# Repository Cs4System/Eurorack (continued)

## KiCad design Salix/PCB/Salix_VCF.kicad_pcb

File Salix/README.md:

# Blattwerk Salix VCF

- VCF based on the Moog Transistor Ladder Filter
- Compensation for loss of bass in high resonance settings via potentiometer
- 6,12,18,24 dB/Oct selectable via potentiometer or CV!
- 2 Inputs with attenuator for audio and CV
- Seperate V/Oct input.
- Input-Drive indicator LED
- 8HP
- small and dense SMD build (0603, SOIC, SOT-363!) Not a beginner build, please be sure to have some SMD-soldering practice!
- 45mA @ +12V and 25mA @ -12V
- quick demo:  https://youtu.be/XMdGtwIK5IQ

- All files are published under CC BY-NC-SA 4.0 
- DO NOT USE COMMERCIALLY!
- Build for yourself or for a friend, but do not sell builds, PCBs, pannels or any parts of the designes in this repository! 
- Feel free to modify, copy and use all files provided here. If you want to publish derivative work, please do so under same license as original

- Any feedback and collaboration is very welcome!
- Please feel free to [open an issue on the issues tab](https://github.com/Cs4System/Eurorack/issues)

## How to get involved:
For ongoing discussion see:
https://www.modwiggler.com/forum/viewtopic.php?f=17&t=244412&p=3457366#p3457366

## Order

- The [original version](https://github.com/Cs4System/Eurorack/tree/main/Transistor_Ladder_VCF) PCB and Panel are be available at [sythCube](https://synthcube.com/cart/lorenz-neumann-diy-transistor-ladder-filter)
- Direct order: If you are interested in a set of PCB+Panel, please write a mail to: blattwerk-audio [at] posteo.de or let me know via [Modwiggler](https://www.modwiggler.com/forum/viewtopic.php?f=17&t=244412&p=3457366#p3457366)

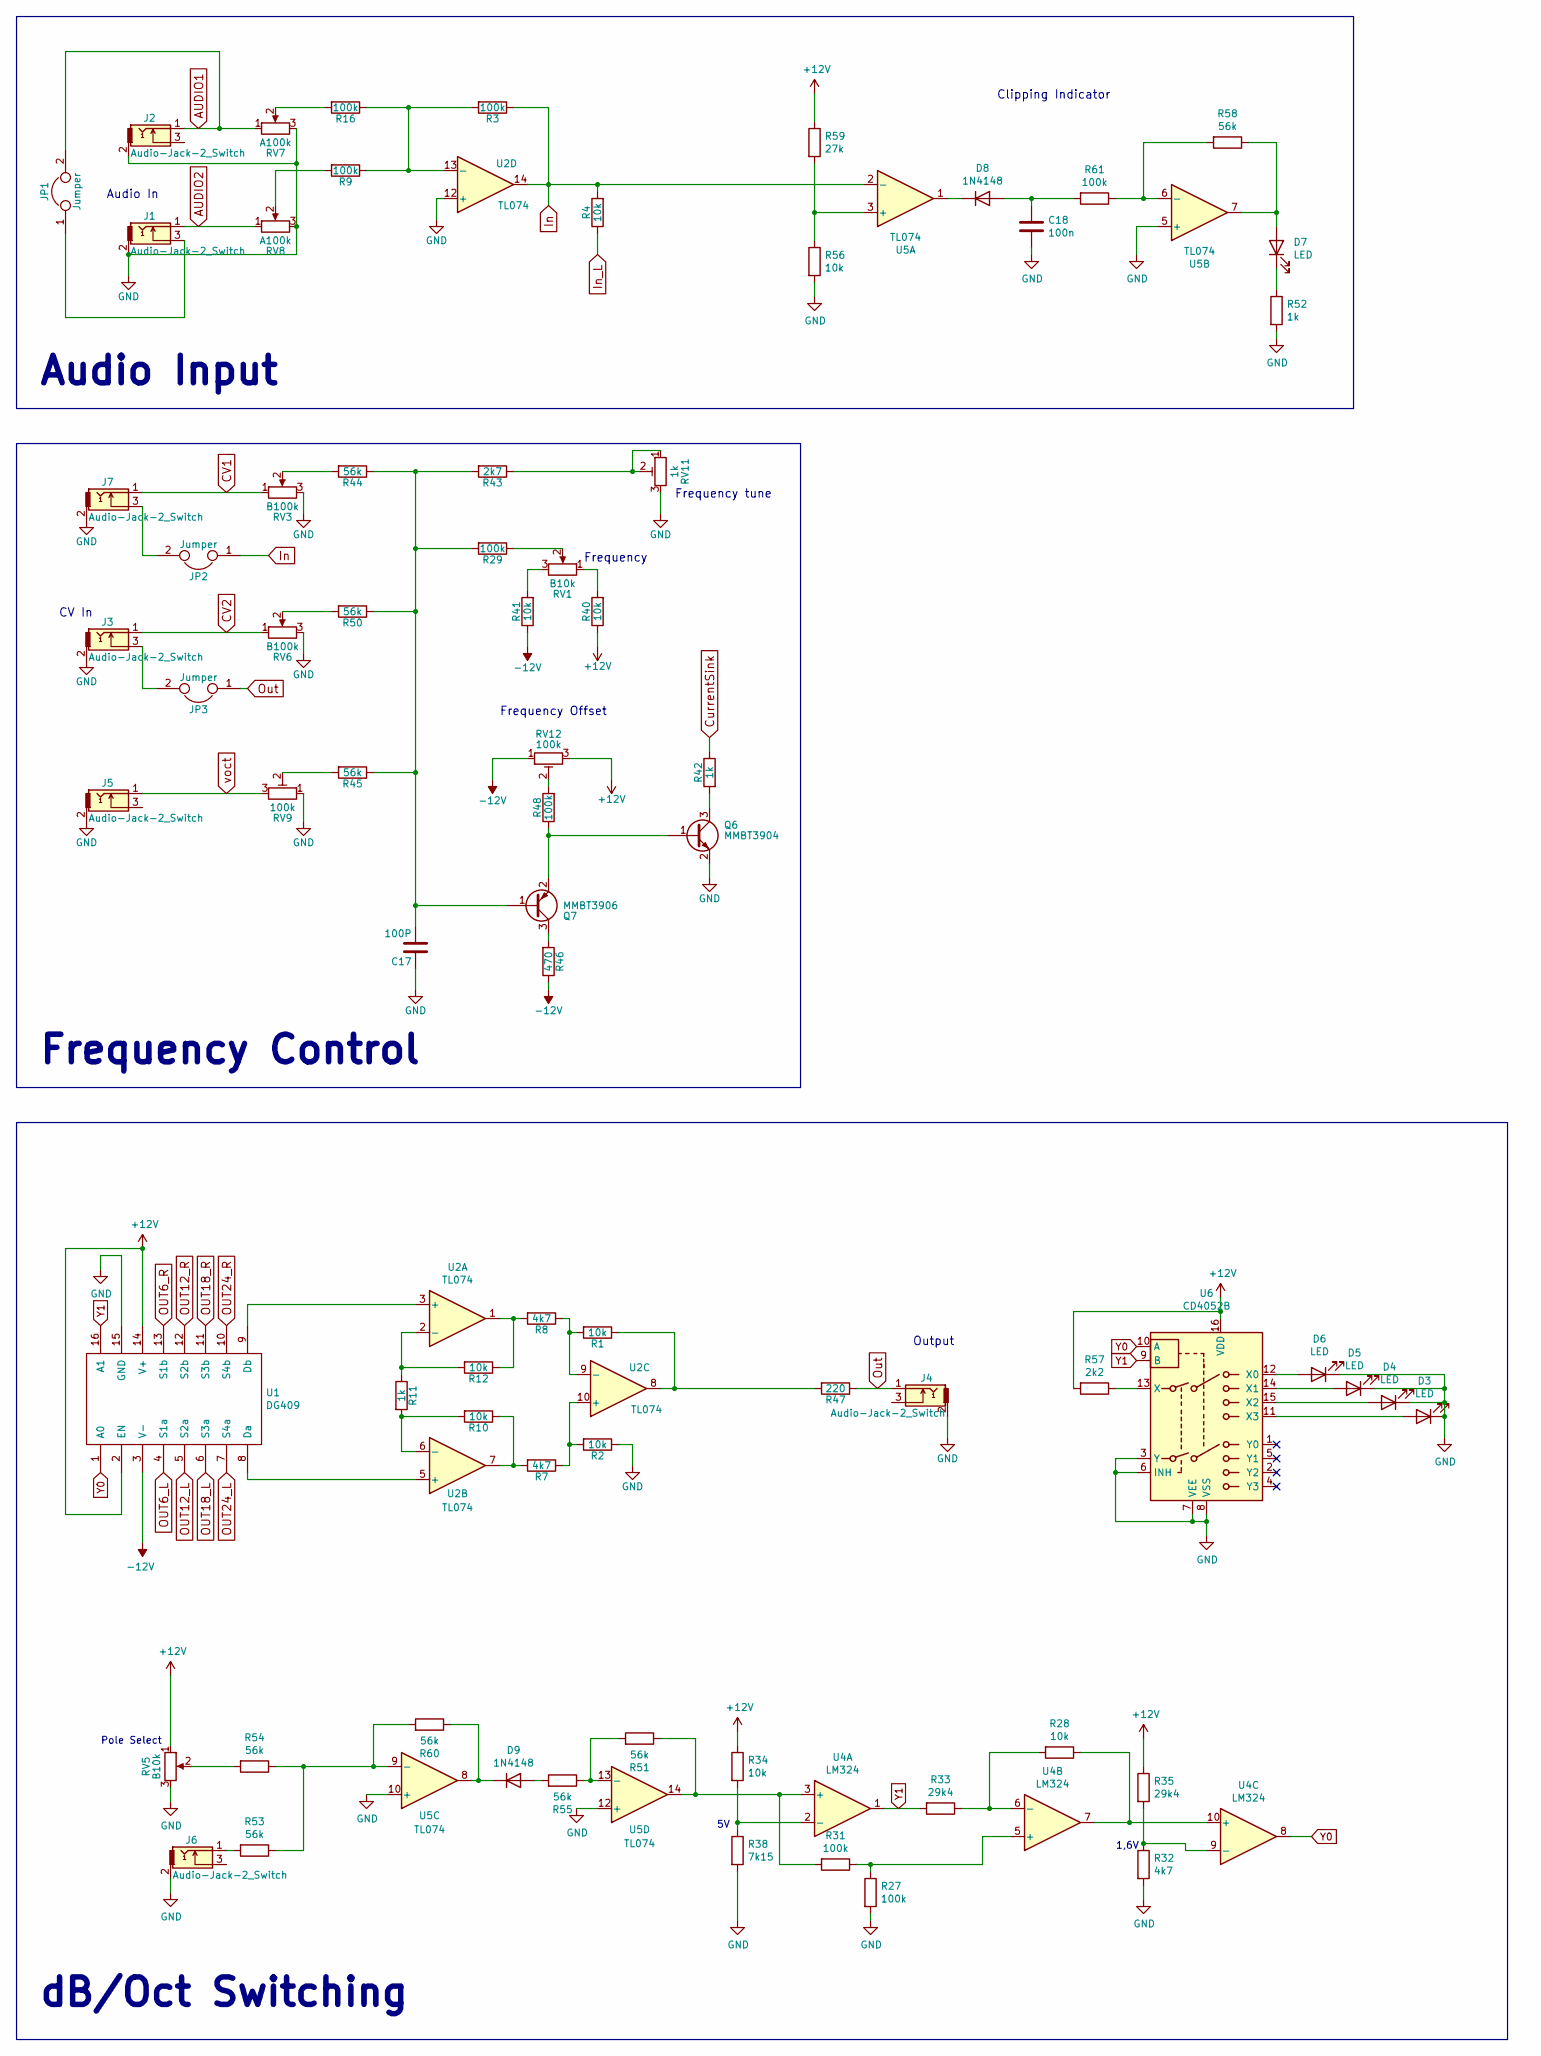
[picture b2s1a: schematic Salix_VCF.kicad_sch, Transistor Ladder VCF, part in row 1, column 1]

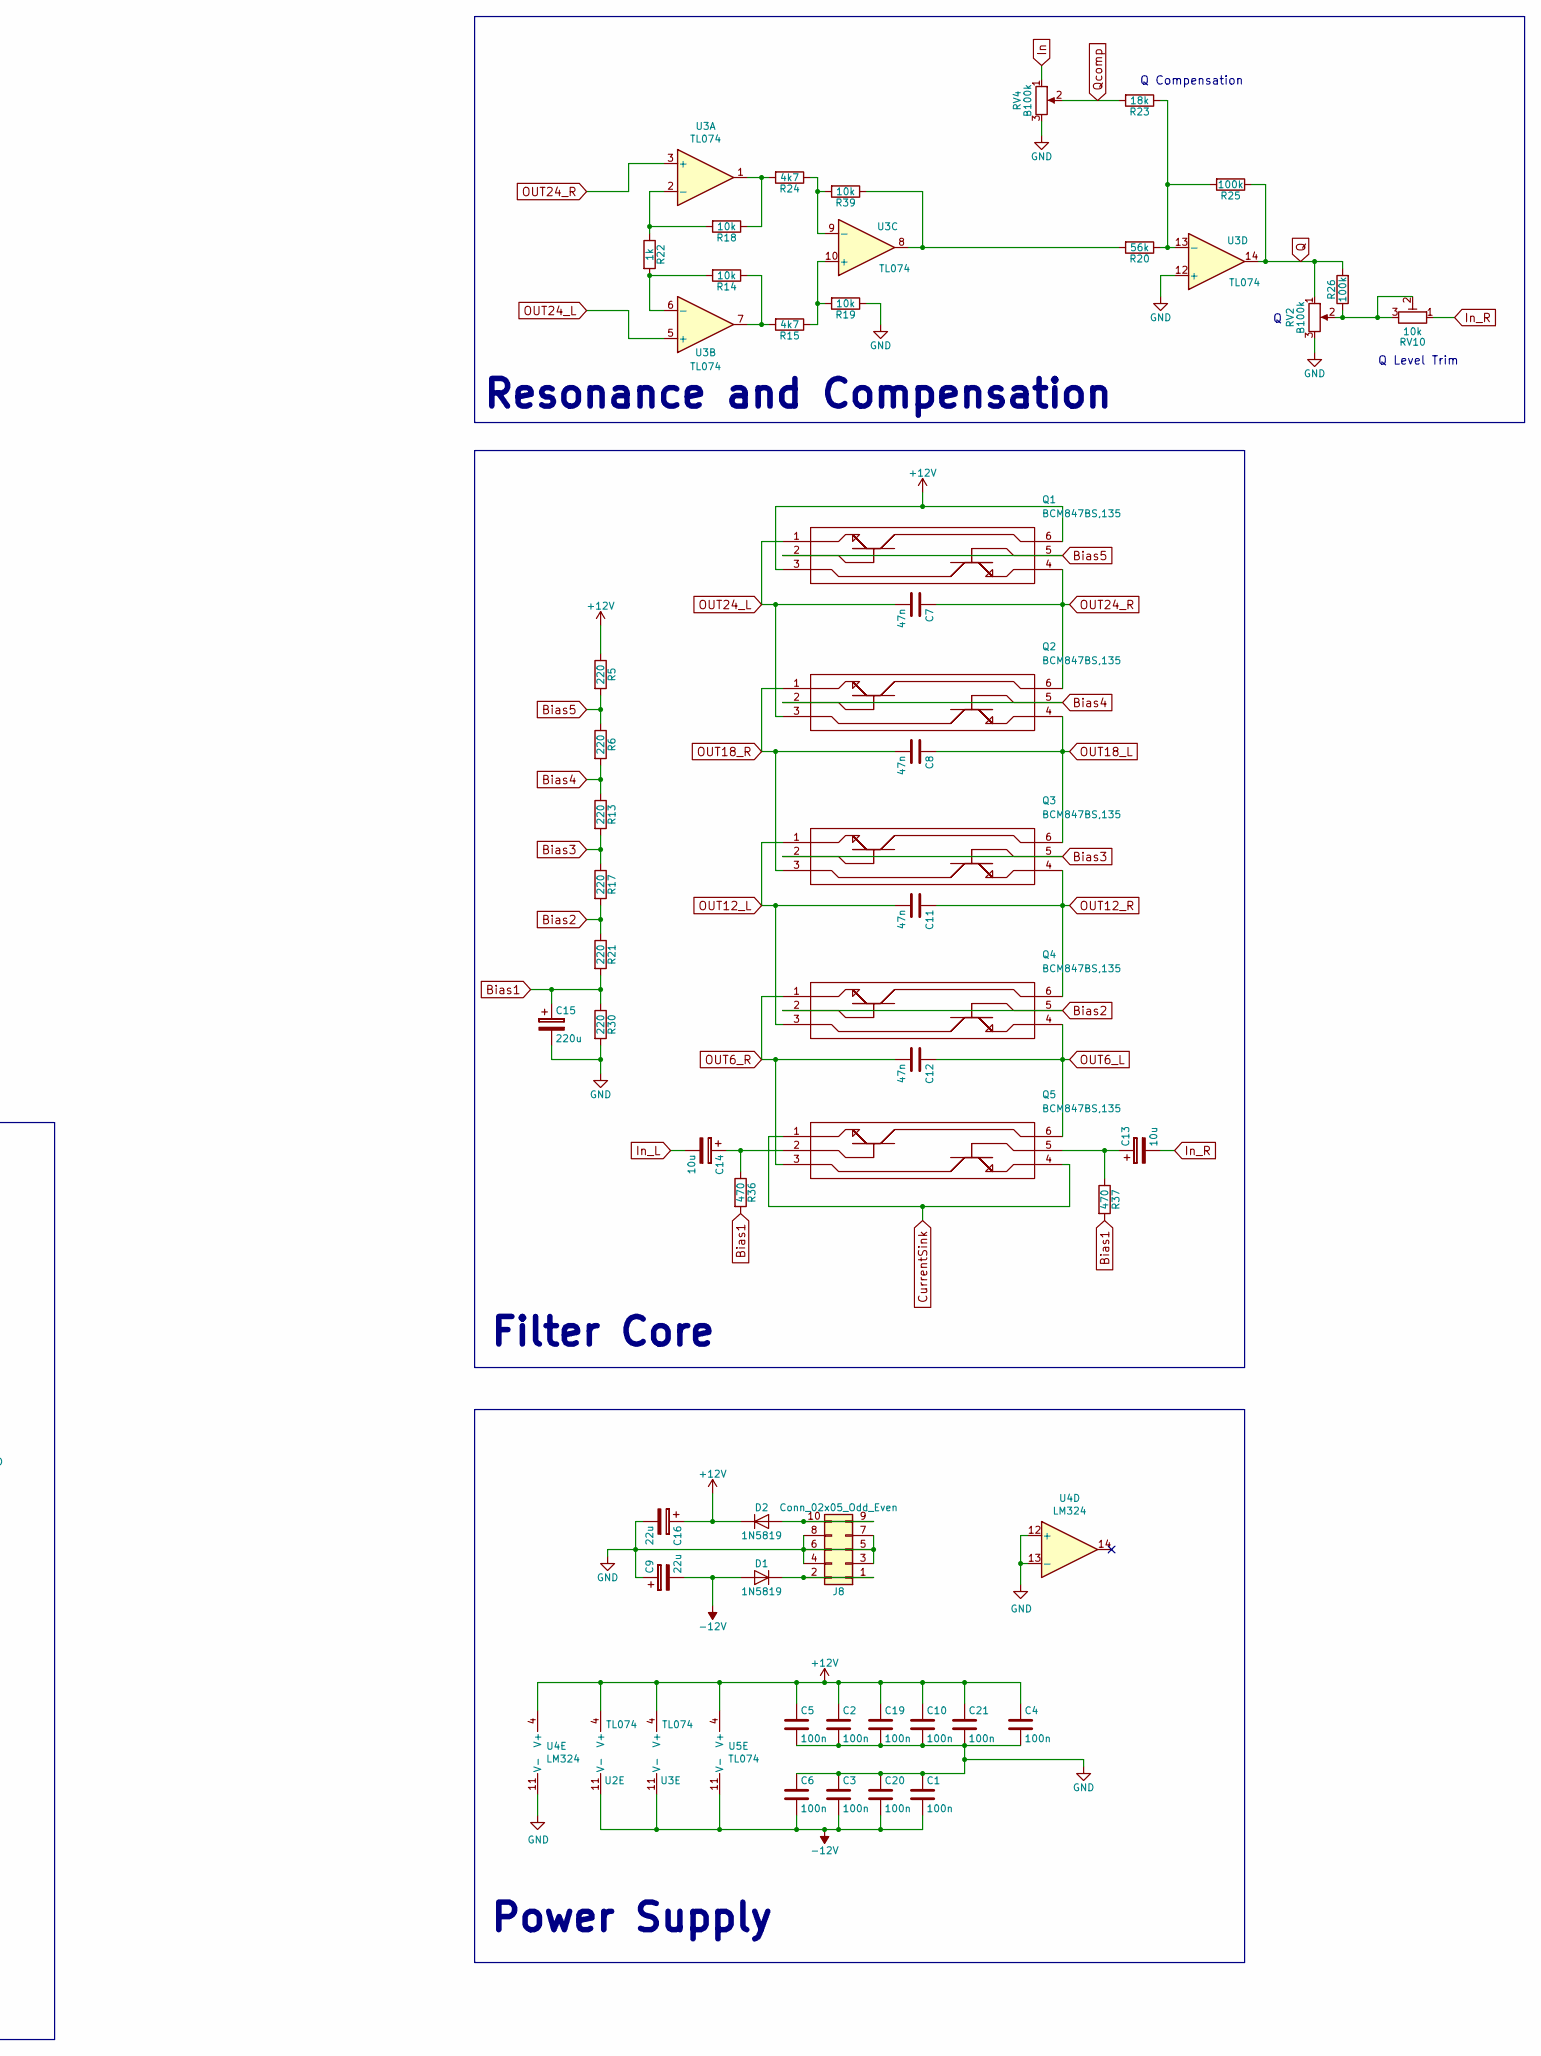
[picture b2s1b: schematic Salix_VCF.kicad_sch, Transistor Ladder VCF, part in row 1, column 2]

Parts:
C1, C2, C3, C4, C5, C6, C10, C18, C19, C20, C21: 100n; C_0603_1608Metric_Pad1.08x0.95mm_HandSolder
C7, C8, C11, C12: 47n; C_Rect_L7.2mm_W2.5mm_P5.00mm_FKS2_FKP2_MKS2_MKP2
C9, C16: 22u; CP_Elec_4x5.7
C13, C14: 10u; CP_Elec_4x5.7
C15: 220u; CP_Elec_6.3x7.7
C17: 100P; C_0603_1608Metric_Pad1.08x0.95mm_HandSolder
D1, D2: 1N5819; D_SOD-123
D3, D4, D5, D6, D7: LED; LED_D3.0mm
D8, D9: 1N4148; D_SOD-323_HandSoldering
J1, J5, J6: Audio-Jack-2_Switch; Thonkicon
J2, J3: Audio-Jack-2_Switch; Thonkicon_noGND
J4: Audio-Jack-2_Switch; Thonkicon_odd
J7: Audio-Jack-2_Switch; Thonkicon_odd2
J8: Conn_02x05_Odd_Even; Multicomp_MC9A12-1034_2x05x2.54mm_Straight
JP1, JP2, JP3: Jumper; PinHeader_1x02_P2.54mm_Vertical
Q1, Q2, Q3, Q4, Q5: BCM847BS,135; SOT-363_SC-70-6_Handsoldering; Manufacturer_Part_Number BCM847BS,135; Mouser Part Number 771-BCM847BS135
Q6: MMBT3904; SOT-23
Q7: MMBT3906; SOT-23
R1, R2, R4, R10, R12, R14, R18, R19, R28, R34, R39, R40, R41, R56: 10k; R_0603_1608Metric_Pad0.98x0.95mm_HandSolder
R3, R9, R16, R25, R26, R27, R29, R31, R48, R61: 100k; R_0603_1608Metric_Pad0.98x0.95mm_HandSolder
R5, R6, R13, R17, R21, R30, R47: 220; R_0603_1608Metric_Pad0.98x0.95mm_HandSolder
R7, R8, R15, R24, R32: 4k7; R_0603_1608Metric_Pad0.98x0.95mm_HandSolder
R11, R22, R42, R52: 1k; R_0603_1608Metric_Pad0.98x0.95mm_HandSolder
R20, R44, R45, R50, R51, R53, R54, R55, R58, R60: 56k; R_0603_1608Metric_Pad0.98x0.95mm_HandSolder
R23: 18k; R_0603_1608Metric_Pad0.98x0.95mm_HandSolder
R33, R35: 29k4; R_0603_1608Metric_Pad0.98x0.95mm_HandSolder
R36, R37, R46: 470; R_0603_1608Metric_Pad0.98x0.95mm_HandSolder
R38: 7k15; R_0603_1608Metric_Pad0.98x0.95mm_HandSolder
R43: 2k7; R_0603_1608Metric_Pad0.98x0.95mm_HandSolder
R57: 2k2; R_0603_1608Metric_Pad0.98x0.95mm_HandSolder
R59: 27k; R_0603_1608Metric_Pad0.98x0.95mm_HandSolder
RV1, RV5: B10k; Potentiometer_Alps_RK09K_Horizontal
RV2, RV3, RV4, RV6: B100k; Potentiometer_Alps_RK09K_Horizontal
RV7, RV8: A100k; Potentiometer_Alps_RK09K_Horizontal
RV9, RV12: 100k; Trim_pot
RV10: 10k; Trim_pot
RV11: 1k; Trim_pot
U1: DG409; SOIC-16_3.9x9.9mm_P1.27mm
U2, U3, U5: TL074; SOIC-14_3.9x8.7mm_P1.27mm
U4: LM324; SOIC-14_3.9x8.7mm_P1.27mm
U6: CD4052B; SOIC-16W_5.3x10.2mm_P1.27mm

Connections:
+12V: C2.1, C4.1, C5.1, C10.1, C16.1, C19.1, C21.1, D2.1 (K), Q1.3, Q1.6, R5.1, R34.1, R35.1, R40.1, R57.2, R59.1, RV5.1, RV12.3, U1.2 (EN), U1.14 (V+), U2.4 (V+), U3.4 (V+), U4.4 (V+), U5.4 (V+), U6.16 (VDD)
-12V: C1.2, C3.2, C6.2, C9.2, C20.2, D1.2 (A), R41.1, R46.1, RV12.1, U1.3 (V-), U2.11 (V-), U3.11 (V-), U5.11 (V-)
AUDIO1: J2.1, JP1.2, RV7.1
AUDIO2: J1.1, RV8.1
Bias1: C15.1, R21.2, R30.1, R36.2, R37.2
Bias2: Q4.2, Q4.5, R17.2, R21.1
Bias3: Q3.2, Q3.5, R13.2, R17.1
Bias4: Q2.2, Q2.5, R6.2, R13.1
Bias5: Q1.2, Q1.5, R5.2, R6.1
CV1: J7.1, RV3.1
CV2: J3.1, RV6.1
CurrentSink: Q5.1, Q5.4, R42.1
GND: C1.1, C2.2, C3.1, C4.2, C5.2, C6.1, C9.1, C10.2, C15.2, C16.2, C17.1, C18.2, C19.2, C20.1, C21.2, D3.1 (K), D4.1 (K), D5.1 (K), D6.1 (K), J1.2, J2.2, J3.2, J4.2, J5.2, J6.2, J7.2, J8.3, J8.4, J8.5, J8.6, J8.7, J8.8, Q6.2 (E), R2.1, R19.1, R27.2, R30.2, R32.2, R38.2, R52.2, R56.2, RV2.3, RV3.3, RV4.3, RV5.3, RV6.3, RV7.3, RV8.3, RV9.1, RV11.3, U1.15 (GND), U2.12 (+), U3.12 (+), U4.11 (V-), U4.12 (+), U4.13 (-), U5.5 (+), U5.10 (+), U5.12 (+), U6.3 (Y), U6.6 (INH), U6.7 (VEE), U6.8 (VSS)
In: JP2.1, R3.1, R4.2, RV4.1, U2.14, U5.2 (-)
In_L: C14.2, R4.1
In_R: C13.2, RV10.1
unnamed: C13.1, Q5.5, R37.1
unnamed: C14.1, Q5.2, R36.1
unnamed: D1.1 (K), J8.1, J8.2
unnamed: D2.2 (A), J8.9, J8.10
unnamed: D3.2 (A), U6.11 (X3)
unnamed: D4.2 (A), U6.15 (X2)
unnamed: D5.2 (A), U6.14 (X1)
unnamed: D6.2 (A), U6.12 (X0)
unnamed: D7.2 (A), R58.1, U5.7
unnamed: D7.1 (K), R52.1
unnamed: C18.1, D8.2 (A), R61.2
unnamed: D8.1 (K), U5.1
unnamed: D9.2 (A), R55.2
unnamed: D9.1 (K), R60.1, U5.8
unnamed: J1.3, JP1.1
unnamed: J3.3, JP3.2
unnamed: J6.1, R53.2
unnamed: J7.3, JP2.2
unnamed: Q6.1 (B), Q7.2 (E), R48.1
unnamed: Q6.3 (C), R42.2
unnamed: C17.2, Q7.1 (B), R29.2, R43.2, R44.1, R45.1, R50.1
unnamed: Q7.3 (C), R46.2
unnamed: R1.1, R47.2, U2.8
unnamed: R9.2, RV8.2
unnamed: R7.2, R10.1, U2.7
unnamed: R8.2, R12.1, U2.1
unnamed: R14.1, R15.2, U3.7
unnamed: R16.2, RV7.2
unnamed: R18.1, R24.2, U3.1
unnamed: R20.2, R39.1, U3.8
unnamed: R26.1, RV2.2, RV10.2, RV10.3
unnamed: R29.1, RV1.2
unnamed: R40.2, RV1.1
unnamed: R41.2, RV1.3
unnamed: R43.1, RV11.1, RV11.2
unnamed: R44.2, RV3.2
unnamed: R45.2, RV9.2
unnamed: R48.2, RV12.2
unnamed: R50.2, RV6.2
unnamed: R54.2, RV5.2
unnamed: U1.8 (Da), U2.5 (+)
unnamed: U1.9 (Db), U2.3 (+)
unnamed: R11.1, R12.2, U2.2 (-)
unnamed: R10.2, R11.2, U2.6 (-)
unnamed: R2.2, R7.1, U2.10 (+)
unnamed: R1.2, R8.1, U2.9 (-)
unnamed: R3.2, R9.1, R16.1, U2.13 (-)
unnamed: R18.2, R22.1, U3.2 (-)
unnamed: R14.2, R22.2, U3.6 (-)
unnamed: R15.1, R19.2, U3.10 (+)
unnamed: R24.1, R39.2, U3.9 (-)
unnamed: R20.1, R23.1, R25.2, U3.13 (-)
unnamed: R31.2, R51.1, U4.3 (+), U5.14
unnamed: R34.2, R38.1, U4.2 (-)
unnamed: R27.1, R31.1, U4.5 (+)
unnamed: R28.2, R33.1, U4.6 (-)
unnamed: R28.1, U4.7, U4.10 (+)
unnamed: R32.1, R35.2, U4.9 (-)
unnamed: R56.1, R59.2, U5.3 (+)
unnamed: R58.2, R61.1, U5.6 (-)
unnamed: R53.1, R54.1, R60.2, U5.9 (-)
unnamed: R51.2, R55.1, U5.13 (-)
unnamed: R57.1, U6.13 (X)
OUT6_L: C12.1, Q4.4, Q5.6, U1.4 (S1a)
OUT6_R: C12.2, Q4.1, Q5.3, U1.13 (S1b)
OUT12_L: C11.2, Q3.1, Q4.3, U1.5 (S2a)
OUT12_R: C11.1, Q3.4, Q4.6, U1.12 (S2b)
OUT18_L: C8.1, Q2.4, Q3.6, U1.6 (S3a)
OUT18_R: C8.2, Q2.1, Q3.3, U1.11 (S3b)
OUT24_L: C7.2, Q1.1, Q2.3, U1.7 (S4a), U3.5 (+)
OUT24_R: C7.1, Q1.4, Q2.6, U1.10 (S4b), U3.3 (+)
Out: J4.1, JP3.1, R47.1
Q: R25.1, R26.2, RV2.1, U3.14
Qcomp: R23.2, RV4.2
Y0: U1.1 (A0), U4.8, U6.10 (A)
Y1: R33.2, U1.16 (A1), U4.1, U6.9 (B)
voct: J5.1, RV9.3

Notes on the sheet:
Audio Input
CV In
Frequency
Power Supply
Frequency Control
Frequency tune
Clipping Indicator
Q Level Trim
Q Compensation
Pole Select
1,6V
Frequency Offset
Output
Audio In
Resonance and Compensation
dB/Oct Switching
Filter Core

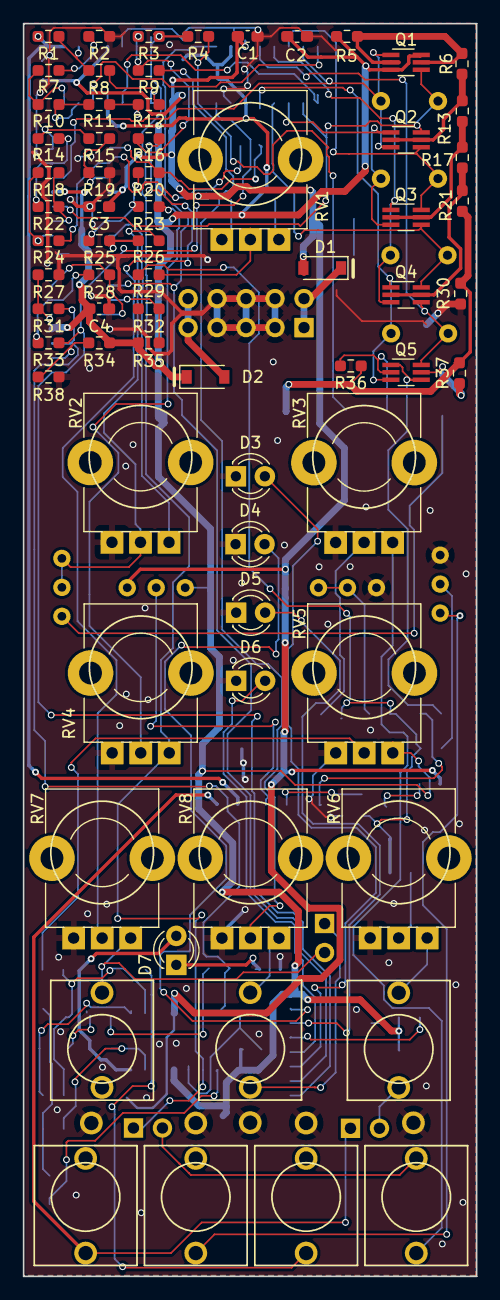
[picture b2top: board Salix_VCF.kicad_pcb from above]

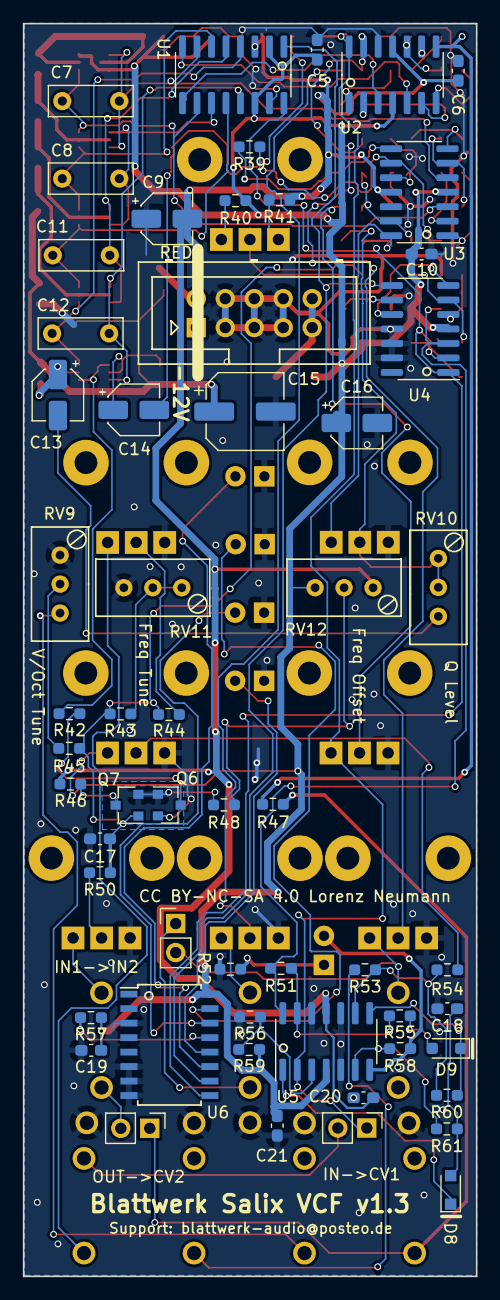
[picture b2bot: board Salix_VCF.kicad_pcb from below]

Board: 2 copper layers, 39.7 x 109.8 mm, 126 parts (57 on the bottom side), 93 nets.

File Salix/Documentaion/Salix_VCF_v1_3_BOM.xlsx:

Name | Housing | Quantity | Value | Mouser | Mouser alternative | Comment
R3,R9,R16,R25,R26,R27,R29,R31,R48,R61 | _0603 | 10 | 100k | 603-RC0603FR-07100KL
R20,R44,R45,R50,R51,R53,R54,R55,R58,R60 | _0603 | 10 | 56k | 603-RC0603FR-0756KL |  | Make R5 and R6 bigger for less CV depth (68k-100k)
R33,R35 | _0603 | 2 | 29k4 | 603-RC0603FR-0729K4L
R59 | _0603 | 1 | 27k | 603-RC0603FR-0727KL
R23 | _0603 | 1 | 18k | 603-RC0603FR-0718KL
R1,R2,R4,R10,R12,R14,R18,R19,R28,R34,R39,R40,R41,R56 | _0603 | 14 | 10k | 603-RC0603FR-0710KL
R38 | _0603 | 1 | 7k15 | 603-RC0603FR-077K15L
R7,R8,R15,R24,R32 | _0603 | 5 | 4k7 | 603-RC0603FR-074K7L
R43 | _0603 | 1 | 2K7 | 603-RC0603FR-072K7L
R57 | _0603 | 2 | 2k2 | 603-RC0603FR-072K2L |  | R49 = 1k8 is fine as well
R11,R22,R42,R52 | _0603 | 4 | 1k | 603-RC0603FR-071KL
R36,R37,R46 | _0603 | 3 | 470R | 603-RC0603FR-07470RL
R5,R6,R13,R17,R21,R30,R47 | _0603 | 7 | 220R | 603-RC0603FR-07220RL
C1,C2,C3,C4,C5,C6,C10,C18,C19,C20,C21 | _0603 | 11 | 100n | 603-CC0603JPX79BB104
C17 | _0603 | 1 | 100p | 710-885012006038
C15 | CP_Elec_6.3x7.7 | 1 | 220u | 140-VZL221M1CTR-0607
C13,C14 | CP_Elec_4x5.7 | 2 | 10u | 667-EEE-1VA100WR
C9,C16 | CP_Elec_4x5.7 | 2 | 22u | 647-UCM1E220MCL1GS
C7,C8,C11,C12 | 7.2x2.5mm P5mm(TH) | 4 | 47n | 505-MKS20.047/63/5
D1,D2 | D_SOD-123 | 2 | 1N5819 | 621-1N5819HW-F
D8,D9 | D_SOD-323 | 2 | 1N4148 | 512-1N4148WS
U2,U3,U5 | SOIC-14_3.9x8.7mm | 3 | TL074 | 511-TL074CDT
U4 | SOIC-14_3.9x8.7mm | 1 | LM324 | 595-LM324ADR
U1 | SOIC-16_3.9x9.9mm | 1 | DG409 | 781-DG409DY-T1-E3 | 700-DG409DY
U6 | SOIC-16_3.9x9.9mm | 1 | CD4052B | 595-CD4052BNSR
Q7 | SOT-23 | 1 | MMBT3906 | 621-MMBT3906-F | any MMBT3906 in SOT23
Q6 | SOT-23 | 1 | MMBT3904 | 621-MMBT3904-F | any MMBT3904 in SOT23
Q1,Q2,Q3,Q4,Q5 | SOT-363 | 5 | BCM847BS,135 | 771-BCM847BS135 |  | Orientation does NOT matter! Small! Be sure to have some SMD practice! (pitch =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
RV9,RV12 | Trimmer_Pitch2.54mm_Multiturn | 2 | 100k | 81-PV36W104C01B00
RV10 | Trimmer_Pitch2.54mm_Multiturn | 1 | 10k | 81-PV36W103C01B00
RV11 | Trimmer_Pitch2.54mm_Multiturn | 1 | 1k | 72-T93YB-1K
RV4,RV6 | Trimmer_RK09K_Horizontal | 2 | B100k | Song Huei Tall Trimmer -> Thonk
RV7,RV8 | Trimmer_RK09K_Horizontal | 2 | A100k | Song Huei Tall Trimmer -> Thonk |  | B100k ist working fine as well, your choice
RV5 | Trimmer_RK09K_Horizontal | 1 | B10k | Song Huei Tall Trimmer -> Thonk
RV2,RV3 | Potentiometer_Alps_RK09K_Horizontal | 2 | B100k | RK09 Type -> Thonk
RV1 | Potentiometer_Alps_RK09K_Horizontal | 1 | B10k | RK09 Type -> Thonk
D3,D4,D5,D6,D7 | LED,3mm | 5 | Red, your choice | 604-WP3A8ID
J1,J2,J3,J4,J5,J6,J7 | Thonkicon | 7 | Audio-Jack-2_Switch
J8 | Pin_Header_Straight_2x05_Pitch2.54mm | 1 | Powerheader
JP1,JP2,JP3 | Pin_Header_Straight_1x02_Pitch2.54mm | 3 | Jumper |  |  | just leave unpoppulated, if not needed, or make solder bridge if permanent is f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
Jumper | Jumper_Pitch2.54mm | 3 | Jumper | 855-M7583-46 |  | just leave unpoppulated, if not needed, or make solder bridge if permanent is f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
Knob | MXR Style | 1 | 25mm | Thonk
Knob | Davies | 2 | 12mm | Thonk
Licence: CC-BY-NC-SA 4.0 @ Lorenz Neumann ***COMMERCIAL USE FORBIDDEN!***
Support and feedback: blattwerk-audio@posteo.de

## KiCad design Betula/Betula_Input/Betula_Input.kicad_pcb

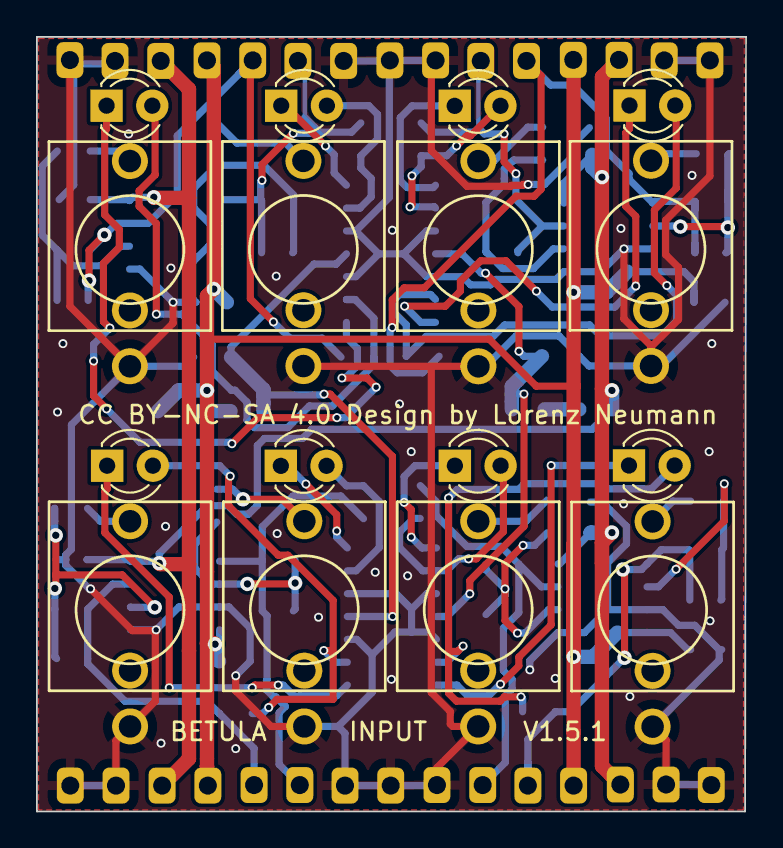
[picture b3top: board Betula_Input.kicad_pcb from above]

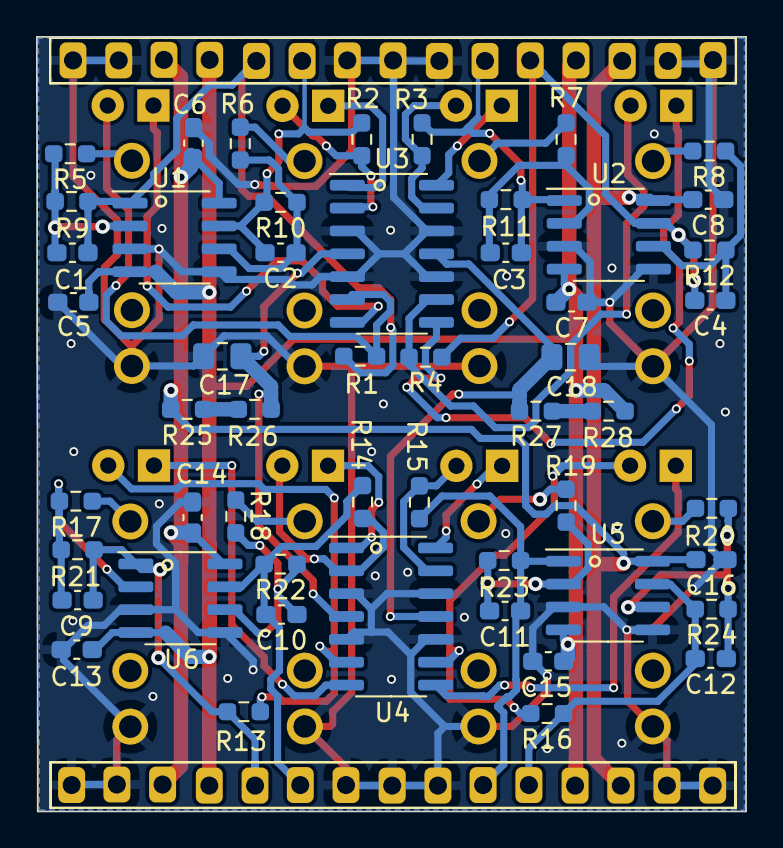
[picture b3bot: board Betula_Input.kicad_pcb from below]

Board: 2 copper layers, 39.4 x 43.0 mm, 69 parts (52 on the bottom side), 47 nets.

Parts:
C1, C2, C3, C4, C9, C10, C11, C12: 560p; C_0603_1608Metric_Pad1.08x0.95mm_HandSolder
C5, C6, C7, C8, C13, C14, C15, C16: 100n; C_0603_1608Metric_Pad1.08x0.95mm_HandSolder
C17, C18: 22u; C_0805_2012Metric_Pad1.18x1.45mm_HandSolder
D1, D2, D3, D4, D5, D6, D7, D8: LED_Dual_Bidirectional; LED_D3.0mm
J1, J2, J3, J4, J5, J6, J7, J8: AudioJack2_SwitchT; Thonkicon
J9: Conn_02x15_Top_Bottom; analogIN-Main
R1, R2, R3, R4, R13, R14, R15, R16: 330R; R_0603_1608Metric_Pad0.98x0.95mm_HandSolder
R5, R6, R7, R8, R17, R18, R19, R20: 22k; R_0603_1608Metric_Pad0.98x0.95mm_HandSolder
R9, R10, R11, R12, R21, R22, R23, R24: 3k3; R_0603_1608Metric_Pad0.98x0.95mm_HandSolder
R25, R26, R27, R28: 47R; R_0603_1608Metric_Pad0.98x0.95mm_HandSolder
U1, U2, U5, U6: OPA1692xD; SOIC-8_3.9x4.9mm_P1.27mm
U3, U4: LM324; SOIC-14_3.9x8.7mm_P1.27mm

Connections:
+12V: C6.2, C8.2, C14.2, C16.2, J9.3, J9.13, J9.18, J9.28, R25.1, U1.8 (V+), U2.8 (V+), U5.8 (V+), U6.8 (V+)
+12VLED: C17.2, R26.2, U3.4 (V+), U4.4 (V+)
-12V: C5.2, C7.2, C13.2, C15.2, J9.4, J9.12, J9.19, J9.27, R28.2, U1.4 (V-), U2.4 (V-), U5.4 (V-), U6.4 (V-)
-12VLED: C18.2, R27.1, U3.11 (V-), U4.11 (V-)
GNDA: C5.1, C6.1, C7.1, C8.1, C13.1, C14.1, C15.1, C16.1, C17.1, C18.1, J1.S, J2.S, J3.S, J4.S, J5.S, J6.S, J7.S, J8.S, J9.1, J9.2, J9.7, J9.8, J9.9, J9.14, J9.15, J9.16, J9.17, J9.22, J9.23, J9.24, J9.29, J9.30, U1.3 (+), U1.5 (+), U2.3 (+), U2.5 (+), U3.3 (+), U3.5 (+), U3.10 (+), U3.12 (+), U4.3 (+), U4.5 (+), U4.10 (+), U4.12 (+), U5.3 (+), U5.5 (+), U6.3 (+), U6.5 (+)
IN1: C4.2, J9.11, R4.1, R12.2, U2.7
IN2: C3.2, J9.10, R3.1, R11.2, U2.1
IN3: C2.2, J9.6, R2.1, R10.2, U1.7
IN4: C1.2, J9.5, R1.1, R9.2, U1.1
IN5: C12.2, J9.26, R16.1, R24.2, U5.7
IN6: C11.2, J9.25, R15.1, R23.2, U5.1
IN7: C10.2, J9.21, R14.1, R22.2, U6.7
IN8: C9.2, J9.20, R13.1, R21.2, U6.1
unnamed: D1.2 (AK), R4.2, U3.9 (-)
unnamed: D1.1 (KA), U3.8
unnamed: D2.2 (AK), R3.2, U3.13 (-)
unnamed: D2.1 (KA), U3.14
unnamed: D3.2 (AK), R2.2, U3.2 (-)
unnamed: D3.1 (KA), U3.1
unnamed: D4.2 (AK), R1.2, U3.6 (-)
unnamed: D4.1 (KA), U3.7
unnamed: D5.2 (AK), R16.2, U4.9 (-)
unnamed: D5.1 (KA), U4.8
unnamed: D6.2 (AK), R15.2, U4.13 (-)
unnamed: D6.1 (KA), U4.14
unnamed: D7.2 (AK), R14.2, U4.2 (-)
unnamed: D7.1 (KA), U4.1
unnamed: D8.2 (AK), R13.2, U4.6 (-)
unnamed: D8.1 (KA), U4.7
unnamed: J1.T, R8.1
unnamed: J2.T, R7.1
unnamed: J3.T, R6.1
unnamed: J4.T, R5.1
unnamed: J5.T, R20.1
unnamed: J6.T, R19.1
unnamed: J7.T, R18.1
unnamed: J8.T, R17.1
unnamed: R25.2, R26.1
unnamed: R27.2, R28.1
unnamed: C1.1, R5.2, R9.1, U1.2 (-)
unnamed: C2.1, R6.2, R10.1, U1.6 (-)
unnamed: C3.1, R7.2, R11.1, U2.2 (-)
unnamed: C4.1, R8.2, R12.1, U2.6 (-)
unnamed: C11.1, R19.2, R23.1, U5.2 (-)
unnamed: C12.1, R20.2, R24.1, U5.6 (-)
unnamed: C9.1, R17.2, R21.1, U6.2 (-)
unnamed: C10.1, R18.2, R22.1, U6.6 (-)

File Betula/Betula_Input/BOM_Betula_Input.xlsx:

Reference(s) | Qty | Value | Footprint | Mouser | Comment
R5,R6,R7,R8,R17,R18,R19,R20 | 8 | 22k | R_0603 | 603-RC0603FR-0722KL
R9, R10, R11, R12, R21, R22, R23, R24 | 8 | 3k3 | R_0603 | 603-RC0603FR-073K3L
R1, R2, R3, R4, R13, R14, R15, R16 | 8 | 330R | R_0603 | 603-RC0603FR-07330RL
R25, R26, R27, R28 | 8 | 47R | R_0603 | 603-RC0603FR-0747RL
C5, C6, C7, C8, C13, C14, C15, C16 | 8 | 100n | C_0603 | 80-C0603C104J5RACLR
C1, C2, C3, C4, C9, C10, C11, C12 | 8 | 560p | C_0603 | 187-CL10C561JB8NFNC | C0G Type!
C17, C18 | 2 | 22u | C_0805 | 187-CL21A226MAYNNNE
U1, U2, U5, U6 | 4 | OPA1692 | SOIC-8_3.9x4.9mm_P1.27mm | 595-OPA1692IDR | TL072C works as well. Higher currend draw ( +6mA on both rails)
U3,U4 | 2 | LM324 | SOIC-14_3.9x8.7mm_P1.27mm | 595-LM324DR
D1, D2, D3, D4, D5, D6, D7, D8 | 8 | LED_Dual_Bidirectional | LED_D3.0mm | 604-WP937EGW
J1, J2, J3, J4, J5, J6, J7, J8 | 8 | AudioJack2_SwitchT |  |  | Thonk
J9 | 2 | 15x1 Pin Header
 |  |  |  |  |  | http://www.ti.com/lit/ds/symlink/ne5532.pdf
 |  |  |  |  |  | http://www.ti.com/lit/ds/symlink/ne5532.pdf
